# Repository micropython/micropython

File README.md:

The MicroPython project
=======================

This is the MicroPython project, an implementation of Python 3.x for
microcontrollers, embedded systems and other constrained platforms.
You can find the official website at [micropython.org](http://www.micropython.org).

MicroPython implements the entire Python 3.4 syntax (including exceptions,
`with`, `yield from`, etc., and additionally `async`/`await` keywords from
Python 3.5 and some select features from later versions). The following core
datatypes are provided: `str`(including basic Unicode support), `bytes`,
`bytearray`, `tuple`, `list`, `dict`, `set`, `frozenset`, `array.array`,
`collections.namedtuple`, classes and instances. Builtin modules include
`os`, `sys`, `time`, `re`, and `struct`, etc. Some ports have support for
`_thread` module (multithreading), `socket` and `ssl` for networking, and
`asyncio`. Note that only a subset of Python 3 functionality is implemented
for the data types and modules.

MicroPython can execute scripts in textual source form (.py files) or from
precompiled bytecode (.mpy files), in both cases either from an on-device
filesystem or "frozen" into the MicroPython executable.

MicroPython also provides a set of MicroPython-specific modules to access
hardware-specific functionality and peripherals such as GPIO, Timers, ADC,
DAC, PWM, SPI, I2C, CAN, Bluetooth, and USB.

Getting started
---------------

See the [online documentation](https://docs.micropython.org/) for the API
reference and information about using MicroPython and information about how
it is implemented.

We use [GitHub Discussions](https://github.com/micropython/micropython/discussions)
as our forum, and [Discord](https://discord.gg/RB8HZSAExQ) for chat. These
are great places to ask questions and advice from the community or to discuss your
MicroPython-based projects.

For bugs and feature requests, please [raise an issue](https://github.com/micropython/micropython/issues/new/choose)
and follow the templates there.

For information about the [MicroPython pyboard](https://store.micropython.org/pyb-features),
the officially supported board from the
[original Kickstarter campaign](https://www.kickstarter.com/projects/214379695/micro-python-python-for-microcontrollers),
see the [schematics and pinouts](http://github.com/micropython/pyboard) and
[documentation](https://docs.micropython.org/en/latest/pyboard/quickref.html).

MicroPython design values
-------------------------

"Perfection is achieved, not when there is nothing more to add, but when there
is nothing left to take away." ―- Antoine de Saint-Exupéry.

For its design and implementation, MicroPython aims to follow a set of values.
Although not a strict set of rules, these values and principles serve as a
useful guide for new and seasoned contributors, as well as maintainers.

MicroPython is at heart a combination of "Micro" and "Python": it's about
resource constrained systems running the Python programming language.  Both of
these concepts balance off against each other in all parts of MicroPython's
design and implementation.

The key concepts that focus the development of MicroPython are:
- Minimalism: do lots with little.
- Efficiency: engineering, build, execution, storage, power consumption.
- Consistency: the whole system feels like it was designed at once.

When using MicroPython, the Python language is used as the human interface to a
system, giving fine control over the entities attached to that system.
In a hardware setting, MicroPython aims to give the user a bare-metal feeling:
one should feel like they have complete control over the system, with very
little between the programmer and the physical world.

MicroPython recognises that systems can be very complex.  The existing Python
libraries in combination with the MicroPython-specific libraries provide a
user-friendly way to harness the complexity of a system.

Python language compatibility is very important to MicroPython, and at first
glance MicroPython should look just like regular Python.  In the first instance,
most Python scripts should run unchanged on MicroPython, even on devices with very
tight resources.  Beyond that, there are ways to extend MicroPython if needed to
better match Python.  The provided built-in modules are an efficient subset of
the corresponding Python ones, without duplication of functionality, and allow
extension in Python if needed.

Contributing
------------

MicroPython is an open-source project and welcomes contributions. To be
productive, please be sure to follow the
[Contributors' Guidelines](https://github.com/micropython/micropython/wiki/ContributorGuidelines)
and the [Code Conventions](https://github.com/micropython/micropython/blob/master/CODECONVENTIONS.md).
Note that MicroPython is licenced under the MIT license, and all contributions
should follow this license.

About this repository
---------------------

This repository contains the following components:
- [py/](py/) -- the core Python implementation, including compiler, runtime, and
  core library.
- [mpy-cross/](mpy-cross/) -- the MicroPython cross-compiler which is used to turn scripts
  into precompiled bytecode.
- [ports/](ports/) -- platform-specific code for the various ports and architectures that MicroPython runs on.
- [lib/](lib/) -- submodules for external dependencies.
- [tests/](tests/) -- test framework and test scripts.
- [docs/](docs/) -- user documentation in Sphinx reStructuredText format. This is used to generate the [online documentation](http://docs.micropython.org).
- [extmod/](extmod/) -- additional (non-core) modules implemented in C.
- [tools/](tools/) -- various tools, including the pyboard.py module.
- [examples/](examples/) -- a few example Python scripts.

"make" is used to build the components, or "gmake" on BSD-based systems.
You will also need bash, gcc, and Python 3.3+ available as the command `python3`.
Some ports (rp2 and esp32) additionally use CMake.

Supported platforms & architectures
-----------------------------------

MicroPython runs on a wide range of microcontrollers, as well as on Unix-like
(including Linux, BSD, macOS, WSL) and Windows systems.

Microcontroller targets can be as small as 256kiB flash + 16kiB RAM, although
devices with at least 512kiB flash + 128kiB RAM allow a much more
full-featured experience.

The [Unix](ports/unix) and [Windows](ports/windows) ports allow both
development and testing of MicroPython itself, as well as providing
lightweight alternative to CPython on these platforms (in particular on
embedded Linux systems).

Over twenty different MicroPython ports are provided in this repository,
split across three
[MicroPython Support Tiers](https://docs.micropython.org/en/latest/develop/support_tiers.html).

Tier 1 Ports
============

👑 Ports in [Tier 1](https://docs.micropython.org/en/latest/develop/support_tiers.html)
are mature and have the most active development, support and testing:

| Port                     | Target                                                                                 | Quick Reference                                                      |
|--------------------------|----------------------------------------------------------------------------------------|----------------------------------------------------------------------|
| [esp32](ports/esp32)*    | Espressif ESP32 SoCs (ESP32, ESP32S2, ESP32S3, ESP32C3, ESP32C6)                       | [here](https://docs.micropython.org/en/latest/esp32/quickref.html)   |
| [mimxrt](ports/mimxrt)   | NXP m.iMX RT                                                                           | [here](https://docs.micropython.org/en/latest/mimxrt/quickref.html)  |
| [rp2](ports/rp2)         | Raspberry Pi RP2040 and RP2350                                                         | [here](https://docs.micropython.org/en/latest/rp2/quickref.html)     |
| [samd](ports/samd)       | Microchip (formerly Atmel) SAMD21 and SAMD51                                           | [here](https://docs.micropython.org/en/latest/samd/quickref.html)    |
| [stm32](ports/stm32)     | STMicroelectronics STM32 MCUs (F0, F4, F7, G0, G4, H5, H7, L0, L1, L4, N6, WB, WL)     | [here](https://docs.micropython.org/en/latest/pyboard/quickref.html) |
| [unix](ports/unix)       | Linux, BSD, macOS, WSL                                                                 | [here](https://docs.micropython.org/en/latest/unix/quickref.html)    |
| [windows](ports/windows) | Microsoft Windows                                                                      | [here](https://docs.micropython.org/en/latest/unix/quickref.html)    |

An asterisk indicates that the port has ongoing financial support from the vendor.

Tier 2 Ports
============

✔ Ports in [Tier 2](https://docs.micropython.org/en/latest/develop/support_tiers.html)
are less mature and less actively developed and tested than Tier 1, but
still fully supported:

| Port                             | Target                                                      | Quick Reference                                                         |
|----------------------------------|-------------------------------------------------------------|-------------------------------------------------------------------------|
| [alif](ports/alif)               | Alif Semiconductor Ensemble MCUs (E3, E7)                   |                                                                         |
| [embed](ports/embed)             | Generates a set of .c/.h files for embedding into a project |                                                                         |
| [nrf](ports/nrf)                 | Nordic Semiconductor nRF51 and nRF52                        |                                                                         |
| [psoc-edge](ports/psoc-edge)     | Infineon PSOC™ Edge                                         | [here](https://docs.micropython.org/en/latest/psoc-edge/quickref.html)  |
| [renesas-ra](ports/renesas-ra)   | Renesas RA family                                           | [here](https://docs.micropython.org/en/latest/renesas-ra/quickref.html) |
| [webassembly](ports/webassembly) | Emscripten port targeting browsers and NodeJS               |                                                                         |
| [zephyr](ports/zephyr)           | Zephyr RTOS                                                 | [here](https://docs.micropython.org/en/latest/zephyr/quickref.html)     |

Tier 3 Ports
============

Ports in [Tier 3](https://docs.micropython.org/en/latest/develop/support_tiers.html)
are built in CI where possible but not regularly tested by the MicroPython maintainers:

| Port                       | Target                                                            | Quick Reference                                                         |
|----------------------------|-------------------------------------------------------------------|-------------------------------------------------------------------------|
| [cc3200](ports/cc3200)     | Texas Instruments CC3200                                          | [For WiPy](https://docs.micropython.org/en/latest/wipy/quickref.html)   |
| [esp8266](ports/esp8266)   | Espressif ESP8266 SoC                                             | [here](https://docs.micropython.org/en/latest/esp8266/quickref.html)    |
| [pic16bit](ports/pic16bit) | Microchip PIC 16-bit                                              |                                                                         |

Additional Ports
================

In addition to the above there is a Tier M containing ports that are used
primarily for maintenance, development and testing:

- The ["bare-arm"](ports/bare-arm) port is an example of the absolute minimum
  configuration that still includes the compiler, and is used to keep track
  of the code size of the core runtime and VM.

- The ["minimal"](ports/minimal) port provides an example of a very basic
  MicroPython port and can be compiled as both a standalone Linux binary as
  well as for ARM Cortex-M4. Start with this if you want to port MicroPython
  to another microcontroller.

- The [qemu](ports/qemu) port is a QEMU-based emulated target for Cortex-A,
  Cortex-M, RISC-V 32-bit, RISC-V 64-bit, and PowerPC 64-bit architectures.

The MicroPython cross-compiler, mpy-cross
-----------------------------------------

Most ports require the [MicroPython cross-compiler](mpy-cross) to be built
first.  This program, called mpy-cross, is used to pre-compile Python scripts
to .mpy files which can then be included (frozen) into the
firmware/executable for a port.  To build mpy-cross use:

    $ cd mpy-cross
    $ make

External dependencies
---------------------

The core MicroPython VM and runtime has no external dependencies, but a given
port might depend on third-party drivers or vendor HALs. This repository
includes [several submodules](lib/) linking to these external dependencies.
Before compiling a given port, use

    $ cd ports/name
    $ make submodules

to ensure that all required submodules are initialised.

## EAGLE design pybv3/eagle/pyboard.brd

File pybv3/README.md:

Schematic, gerbers, EAGLE files, BOM and assembly guide for PYBv3.

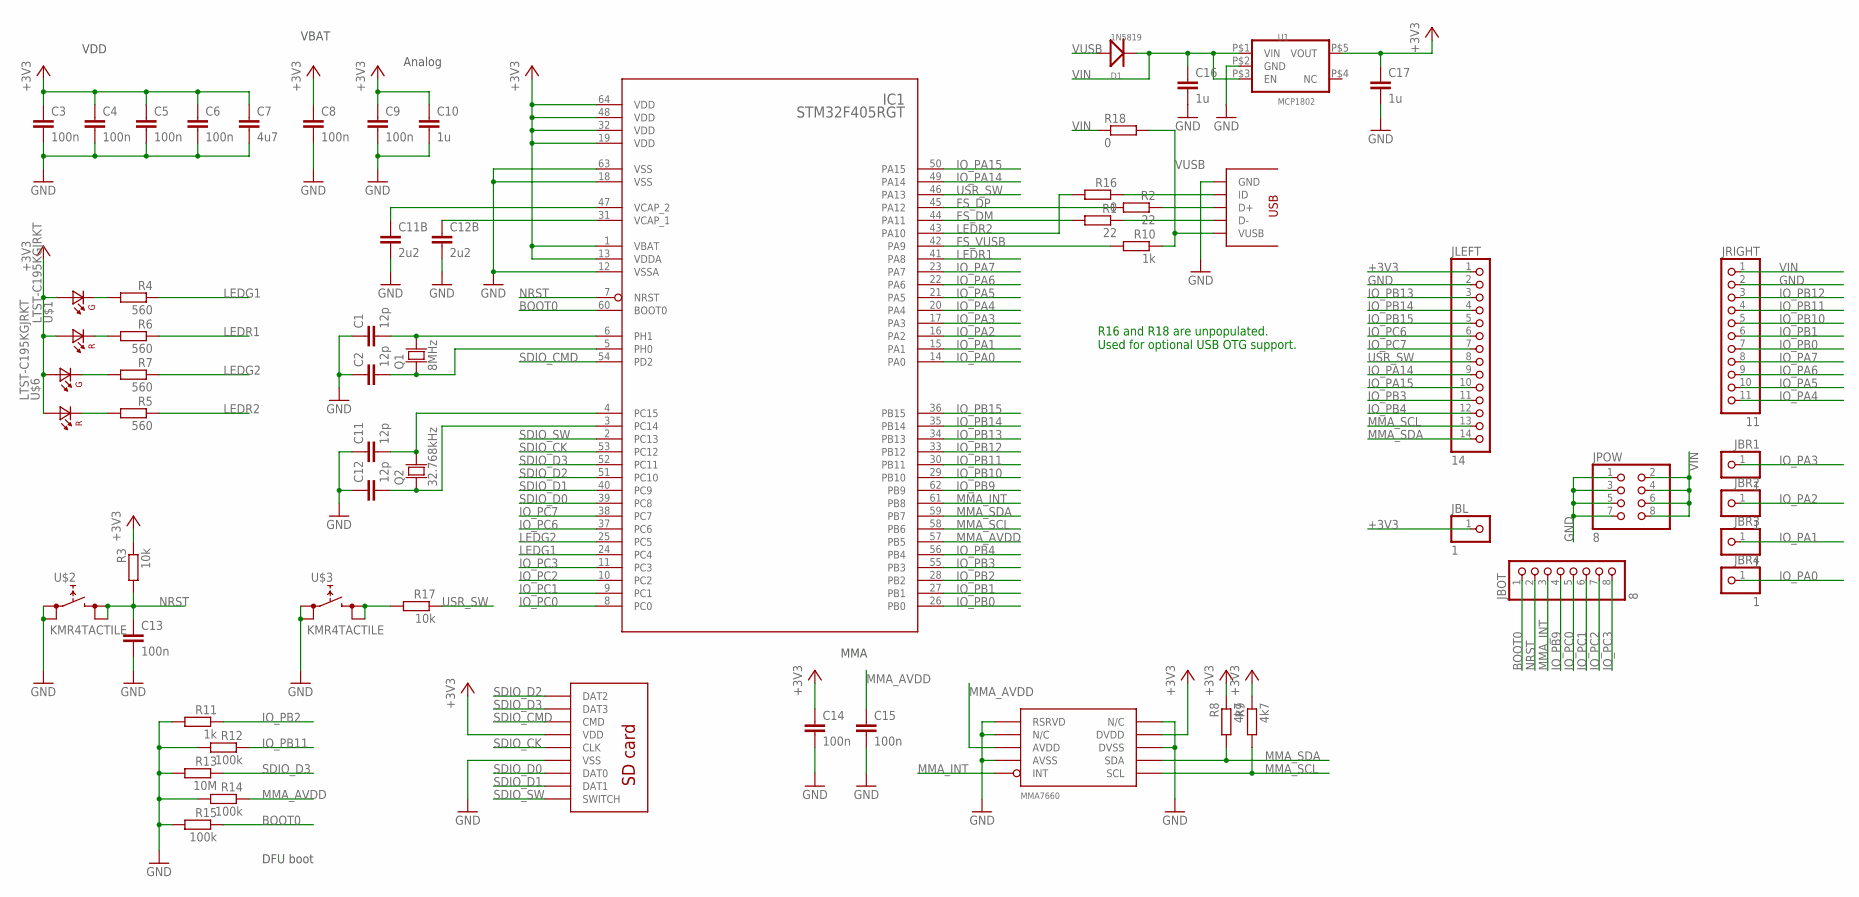
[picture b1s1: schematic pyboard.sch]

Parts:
C1, C2, C11, C12: 12p; C0603
C3, C4, C5, C6, C8, C9, C13, C14, C15: 100n; C0603
C7: 4u7; C0603
C10, C16, C17: 1u; C0603
C11B, C12B: 2u2; C0603
D1: 1N5819; SOD-123
IC1: STM32F405RGT; LQFP64
JBL: 1; 1X01
JBOT: 8; 1X08
JBR1, JBR2, JBR3, JBR4: 1; 1X01
JLEFT: 14; 1X14
JPOW: 8; 2X04
JRIGHT: 11; 1X11
Q1: 8MHz; TXC-SMD-50X32
Q2: 32.768kHz; TXC-SMD-32X15
R1, R2: 22; R0603
R3, R17: 10k; R0603
R4, R5, R6, R7: 560; R0603
R8, R9: 4k7; R0603
R10, R11: 1k; R0603
R12, R14, R15: 100k; R0603
R13: 10M; R0603
R16: 0; R0603
R18: 0; R0805
U1: MCP1802; SOT-23-5
U$1, U$6: LTST-C195KGJRKT; LTST-BILED-15X16
U$2, U$3: KMR4TACTILE; KMR4SWITCH
U$4: MOLEX-SD-105027; MOLEX-SD-105027-PKG
U$5: MMA7660; DFN10
U$7: USB-MICRO-AB; HRS-USB-ZX62D-AB-5P8-PKG

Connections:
+3V3: C3.1, C4.1, C5.1, C6.1, C7.1, C8.1, C9.1, C10.1, C14.1, C17.1, IC1.1 (VBAT), IC1.13 (VDDA), IC1.19 (VDD), IC1.32 (VDD), IC1.48 (VDD), IC1.64 (VDD), JBL.1, JLEFT.1, R3.1, R8.1, R9.1, U1.P$5 (VOUT), U$1.P$1 (A1), U$1.P$2 (A2), U$4.P$4 (VDD), U$5.P$9 (DVDD), U$6.P$1 (A1), U$6.P$2 (A2)
BOOT0: IC1.60 (BOOT0), JBOT.1, R15.1
FS_DM: IC1.44 (PA11), R1.2
FS_DP: IC1.45 (PA12), R2.2
FS_VUSB: IC1.42 (PA9), R10.2
GND: C1.1, C2.1, C3.2, C4.2, C5.2, C6.2, C7.2, C8.2, C9.2, C10.2, C11.1, C11B.2, C12.1, C12B.2, C13.2, C14.2, C15.2, C16.2, C17.2, IC1.12 (VSSA), IC1.18 (VSS), IC1.63 (VSS), JLEFT.2, JPOW.1, JPOW.3, JPOW.5, JPOW.7, JRIGHT.2, R11.2, R12.2, R13.2, R14.2, R15.2, U1.P$2 (GND), U$2.P$1 (0), U$2.P$2 (0), U$3.P$1 (0), U$3.P$2 (0), U$4.P$6 (VSS), U$5.P$1 (RSRVD), U$5.P$2 (N/C), U$5.P$4 (AVSS), U$5.P$8 (DVSS), U$5.P$10 (N/C), U$7.P$5 (GND)
IO_PA0: IC1.14 (PA0), JBR4.1
IO_PA1: IC1.15 (PA1), JBR3.1
IO_PA2: IC1.16 (PA2), JBR2.1
IO_PA3: IC1.17 (PA3), JBR1.1
IO_PA4: IC1.20 (PA4), JRIGHT.11
IO_PA5: IC1.21 (PA5), JRIGHT.10
IO_PA6: IC1.22 (PA6), JRIGHT.9
IO_PA7: IC1.23 (PA7), JRIGHT.8
IO_PA14: IC1.49 (PA14), JLEFT.9
IO_PA15: IC1.50 (PA15), JLEFT.10
IO_PB0: IC1.26 (PB0), JRIGHT.7
IO_PB1: IC1.27 (PB1), JRIGHT.6
IO_PB2: IC1.28 (PB2), R11.1
IO_PB3: IC1.55 (PB3), JLEFT.11
IO_PB4: IC1.56 (PB4), JLEFT.12
IO_PB9: IC1.62 (PB9), JBOT.4
IO_PB10: IC1.29 (PB10), JRIGHT.5
IO_PB11: IC1.30 (PB11), JRIGHT.4, R12.1
IO_PB12: IC1.33 (PB12), JRIGHT.3
IO_PB13: IC1.34 (PB13), JLEFT.3
IO_PB14: IC1.35 (PB14), JLEFT.4
IO_PB15: IC1.36 (PB15), JLEFT.5
IO_PC0: IC1.8 (PC0), JBOT.5
IO_PC1: IC1.9 (PC1), JBOT.6
IO_PC2: IC1.10 (PC2), JBOT.7
IO_PC3: IC1.11 (PC3), JBOT.8
IO_PC6: IC1.37 (PC6), JLEFT.6
IO_PC7: IC1.38 (PC7), JLEFT.7
LEDG1: IC1.24 (PC4), R4.1
LEDG2: IC1.25 (PC5), R7.1
LEDR1: IC1.41 (PA8), R6.1
LEDR2: IC1.43 (PA10), R5.1, R16.2
MMA_AVDD: C15.1, IC1.57 (PB5), R14.1, U$5.P$3 (AVDD)
MMA_INT: IC1.61 (PB8), JBOT.3, U$5.P$5 (INT)
MMA_SCL: IC1.58 (PB6), JLEFT.13, R9.2, U$5.P$6 (SCL)
MMA_SDA: IC1.59 (PB7), JLEFT.14, R8.2, U$5.P$7 (SDA)
unnamed: C11B.1, IC1.47 (VCAP_2)
unnamed: C12B.1, IC1.31 (VCAP_1)
unnamed: R2.1, U$7.P$3 (D+)
unnamed: R1.1, U$7.P$2 (D-)
unnamed: C12.2, IC1.3 (PC14), Q2.P$1
unnamed: C11.2, IC1.4 (PC15), Q2.P$2
unnamed: R16.1, U$7.P$4 (ID)
unnamed: C1.2, IC1.6 (PH1), Q1.P$2
unnamed: C2.2, IC1.5 (PH0), Q1.P$1
unnamed: R4.2, U$1.P$3 (K1)
unnamed: R5.2, U$6.P$4 (K2)
unnamed: R6.2, U$1.P$4 (K2)
unnamed: R7.2, U$6.P$3 (K1)
unnamed: R17.2, U$3.P$3 (1), U$3.P$4 (1)
NRST: C13.1, IC1.7 (NRST), JBOT.2, R3.2, U$2.P$3 (1), U$2.P$4 (1)
SDIO_CK: IC1.53 (PC12), U$4.P$5 (CLK)
SDIO_CMD: IC1.54 (PD2), U$4.P$3 (CMD)
SDIO_D0: IC1.39 (PC8), U$4.P$7 (DAT0)
SDIO_D1: IC1.40 (PC9), U$4.P$8 (DAT1)
SDIO_D2: IC1.51 (PC10), U$4.P$1 (DAT2)
SDIO_D3: IC1.52 (PC11), R13.1, U$4.P$2 (DAT3)
SDIO_SW: IC1.2 (PC13), U$4.G$1 (SWITCH)
USR_SW: IC1.46 (PA13), JLEFT.8, R17.1
VIN: C16.1, D1.K, JPOW.2, JPOW.4, JPOW.6, JPOW.8, JRIGHT.1, R18.1, U1.P$1 (VIN), U1.P$3 (EN)
VUSB: D1.A, R10.1, R18.2, U$7.P$1 (VUSB)

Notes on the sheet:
Analog
DFU boot
MMA
VBAT
VDD
R16 and R18 are unpopulated. Used for optional USB OTG support.

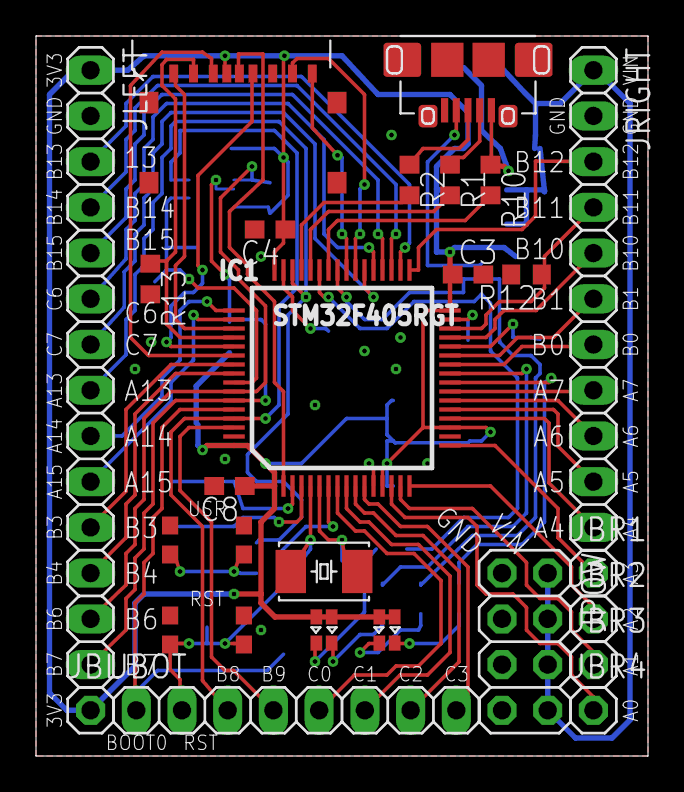
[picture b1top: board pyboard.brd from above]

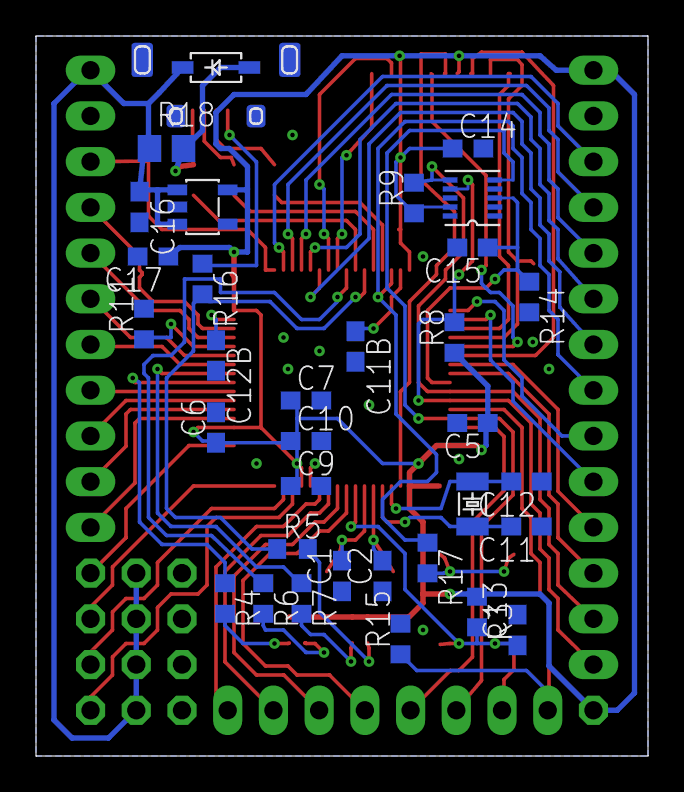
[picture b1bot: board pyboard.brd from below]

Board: 2 copper layers, 34.0 x 40.0 mm, 58 parts (33 on the bottom side), 67 nets.
